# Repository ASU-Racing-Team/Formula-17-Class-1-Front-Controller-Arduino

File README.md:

# ASU Racing Team Formula Students 2017 Class 1 Sensor Data Acquisition Module
Uses an Atmega32 microcontroller with the Arduino Environment and FreeRTOS to read 4 suspension travel sensors, a steering position sensor, a speed sensor and MPU9250 IMU

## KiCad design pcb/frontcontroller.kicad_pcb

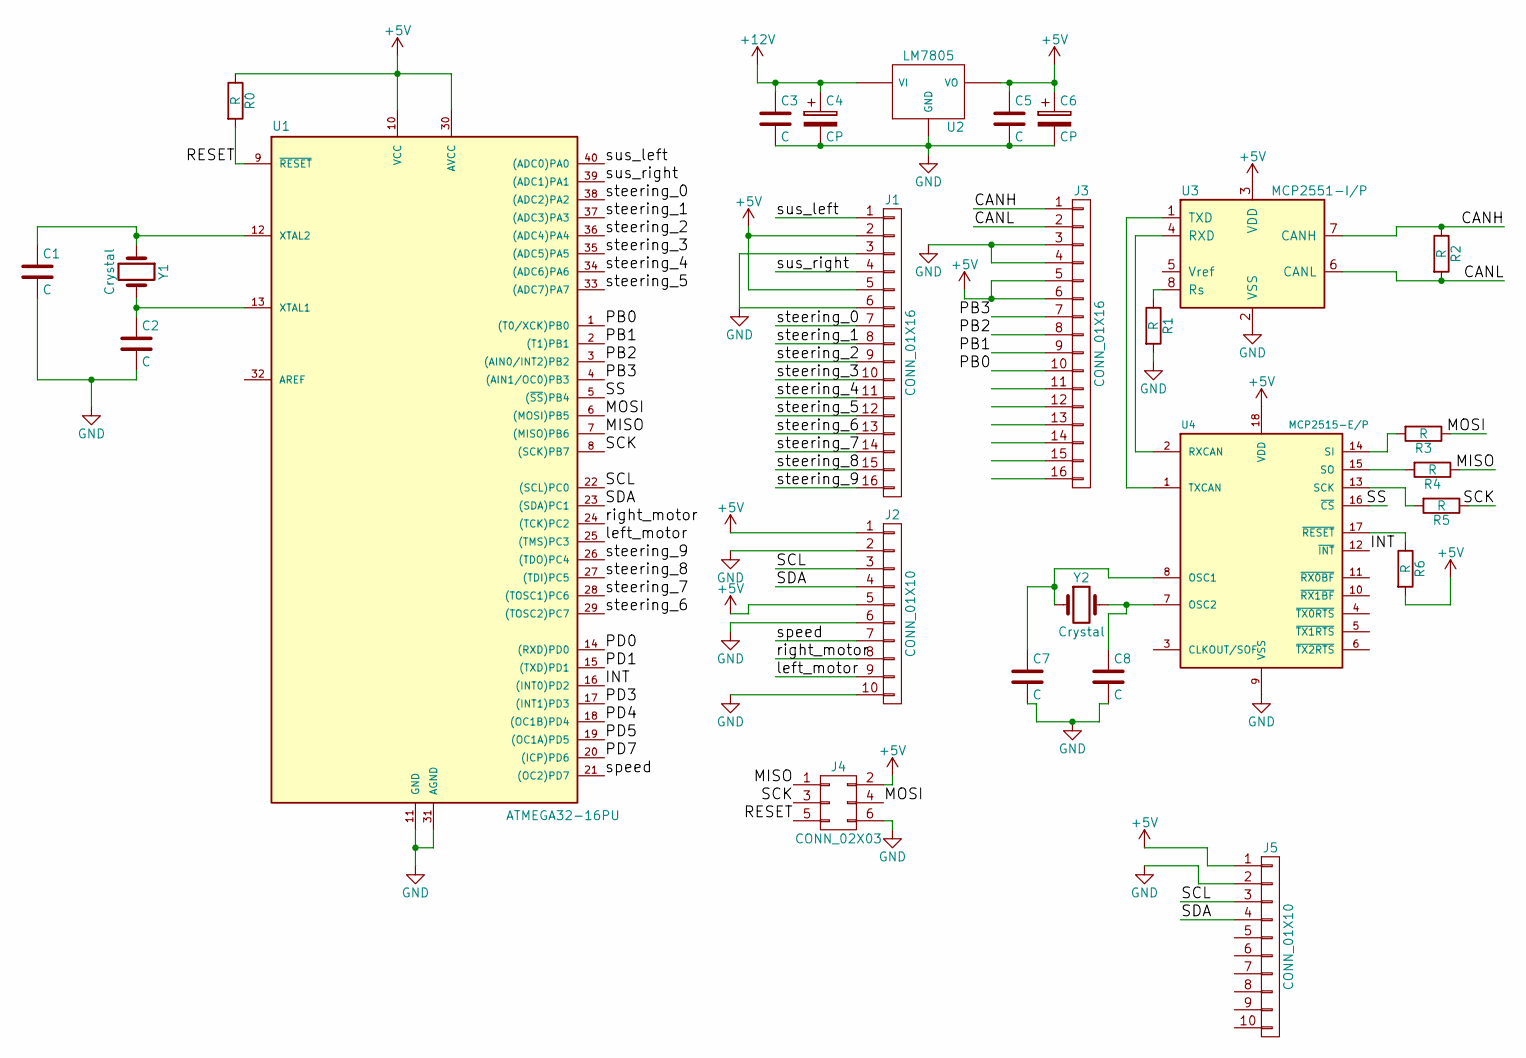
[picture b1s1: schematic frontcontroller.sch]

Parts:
C1, C2, C3, C5, C7, C8: C; C_Disc_D3.4mm_W2.1mm_P2.50mm
C4, C6: CP; CP_Radial_D8.0mm_P3.50mm
J1, J3: CONN_01X16; Pin_Header_Straight_1x16_Pitch2.54mm
J2, J5: CONN_01X10; Pin_Header_Straight_1x10_Pitch2.54mm
J4: CONN_02X03; Pin_Header_Straight_2x03_Pitch2.54mm
R0, R1, R2, R3, R4, R5, R6: R; R_Axial_DIN0204_L3.6mm_D1.6mm_P2.54mm_Vertical
U1: ATMEGA32-16PU; DIP-40_W15.24mm
U2: LM7805; TO-220_Vertical
U3: MCP2551-I/P; DIP-8_W7.62mm_Socket
U4: MCP2515-E/P; DIP-18_W7.62mm_Socket
Y1, Y2: Crystal; Crystal_HC49-U_Vertical

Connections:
+5V: C5.1, C6.1, J1.2, J1.5, J2.1, J2.5, J3.5, J3.6, J4.2, J5.1, R0.1, R6.2, U1.10 (VCC), U1.30 (AVCC), U2.3 (VO), U3.3 (VDD), U4.18 (VDD)
+12V: C3.1, C4.1, U2.1 (VI)
/CANH: J3.1, R2.1, U3.7 (CANH)
/CANL: J3.2, R2.2, U3.6 (CANL)
/INT: U1.16 ((INT0)PD2), U4.12 (~INT~)
/MISO: J4.1, R4.1, U1.7 ((MISO)PB6)
/MOSI: J4.4, R3.1, U1.6 ((MOSI)PB5)
/PB0: J3.10, U1.1 ((T0/XCK)PB0)
/PB1: J3.9, U1.2 ((T1)PB1)
/PB2: J3.8, U1.3 ((AIN0/INT2)PB2)
/PB3: J3.7, U1.4 ((AIN1/OC0)PB3)
/PD0: U1.14 ((RXD)PD0)
/PD1: U1.15 ((TXD)PD1)
/PD3: U1.17 ((INT1)PD3)
/PD4: U1.18 ((OC1B)PD4)
/PD5: U1.19 ((OC1A)PD5)
/PD7: U1.20 ((ICP)PD6)
/RESET: J4.5, R0.2, U1.9 (~RESET)
/SCK: J4.3, R5.1, U1.8 ((SCK)PB7)
/SCL: J2.3, J5.3, U1.22 ((SCL)PC0)
/SDA: J2.4, J5.4, U1.23 ((SDA)PC1)
/SS: U1.5 ((~SS~)PB4), U4.16 (~CS~)
/left_motor: J2.9, U1.25 ((TMS)PC3)
/right_motor: J2.8, U1.24 ((TCK)PC2)
/speed: J2.7, U1.21 ((OC2)PD7)
/steering_0: J1.7, U1.38 ((ADC2)PA2)
/steering_1: J1.8, U1.37 ((ADC3)PA3)
/steering_2: J1.9, U1.36 ((ADC4)PA4)
/steering_3: J1.10, U1.35 ((ADC5)PA5)
/steering_4: J1.11, U1.34 ((ADC6)PA6)
/steering_5: J1.12, U1.33 ((ADC7)PA7)
/steering_6: J1.13, U1.29 ((TOSC2)PC7)
/steering_7: J1.14, U1.28 ((TOSC1)PC6)
/steering_8: J1.15, U1.27 ((TDI)PC5)
/steering_9: J1.16, U1.26 ((TDO)PC4)
/sus_left: J1.1, U1.40 ((ADC0)PA0)
/sus_right: J1.4, U1.39 ((ADC1)PA1)
GND: C1.2, C2.2, C3.2, C4.2, C5.2, C6.2, C7.2, C8.2, J1.3, J1.6, J2.2, J2.6, J2.10, J3.3, J3.4, J4.6, J5.2, R1.2, U1.11 (GND), U1.31 (AGND), U2.2 (GND), U3.2 (VSS), U4.9 (VSS)
unnamed: C1.1, U1.12 (XTAL2), Y1.1
unnamed: C2.1, U1.13 (XTAL1), Y1.2
unnamed: C7.1, U4.8 (OSC1), Y2.1
unnamed: C8.1, U4.7 (OSC2), Y2.2
unnamed: R1.1, U3.8 (Rs)
unnamed: R3.2, U4.14 (SI)
unnamed: R4.2, U4.15 (SO)
unnamed: R5.2, U4.13 (SCK)
unnamed: R6.1, U4.17 (~RESET~)
unnamed: U3.1 (TXD), U4.1 (TXCAN)
unnamed: U3.4 (RXD), U4.2 (RXCAN)

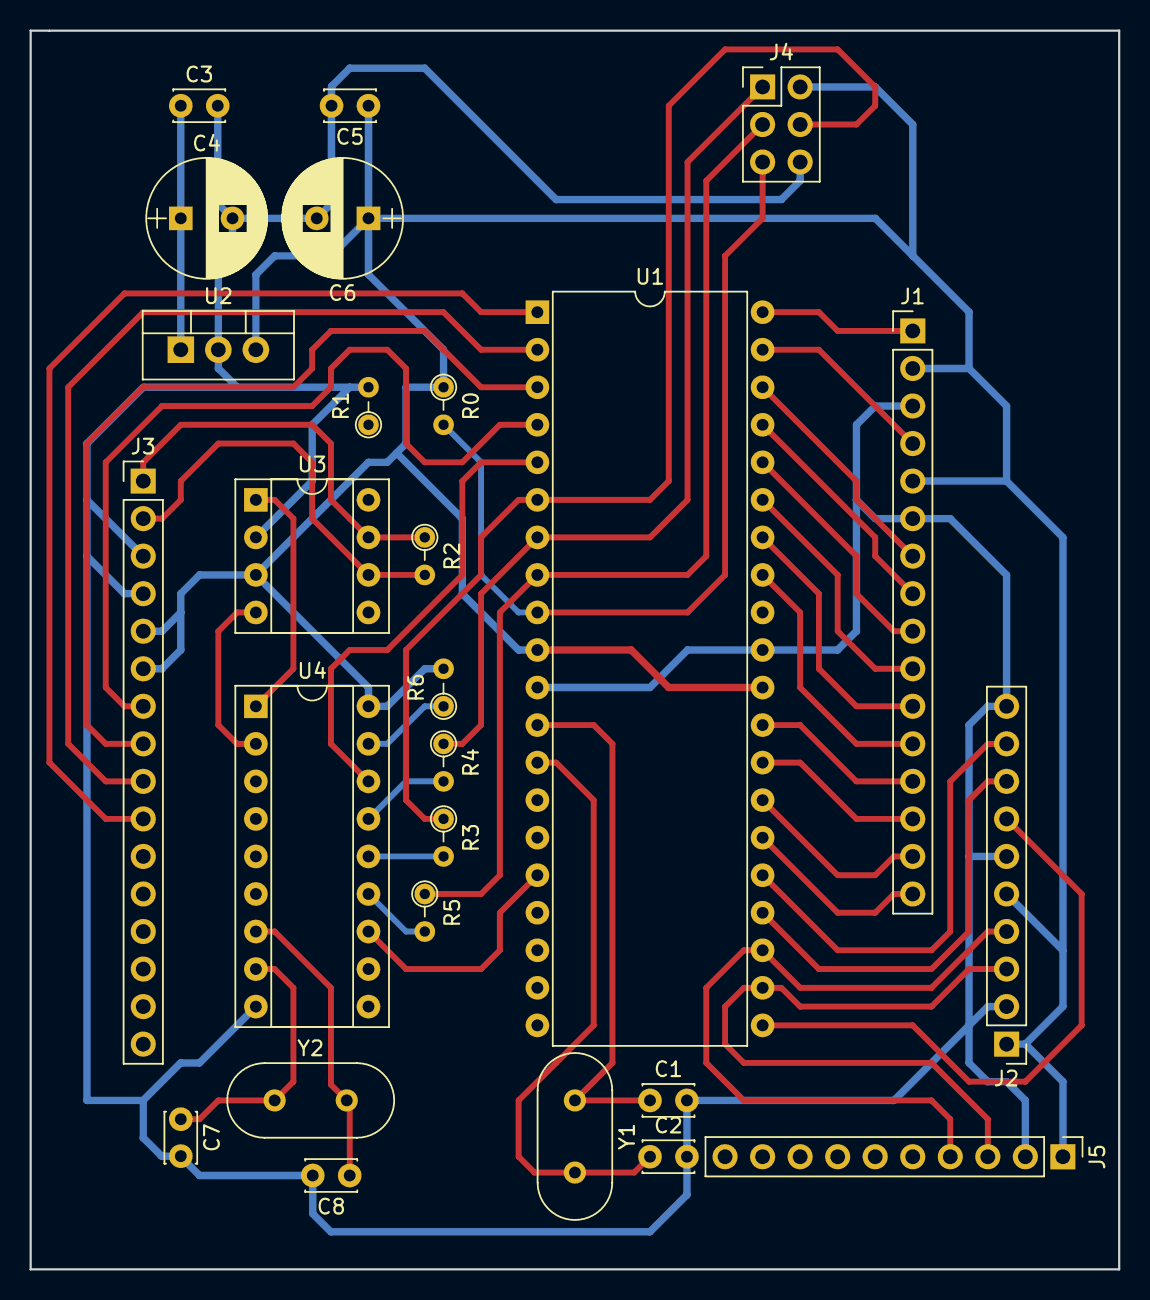
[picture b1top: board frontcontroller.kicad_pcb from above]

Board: 2 copper layers, 73.7 x 83.8 mm, 26 parts (0 on the bottom side), 43 nets.

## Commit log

2017-09-09 initial
